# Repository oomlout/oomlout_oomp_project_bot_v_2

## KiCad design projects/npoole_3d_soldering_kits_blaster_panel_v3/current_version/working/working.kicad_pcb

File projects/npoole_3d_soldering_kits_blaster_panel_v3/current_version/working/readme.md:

# 3d_soldering_kits
 
## summary 
* id: npoole_3d_soldering_kits_blaster_panel_v3
* user: npoole
* name: 3d_soldering_kits
* board: blaster_panel_v3
* repo: https://github.com/NPoole/3D-Soldering-Kits

* src_file_repo_sch: 
* src_file_repo_sch_link: https://github.com/NPoole/3D-Soldering-Kits/tree/master/
* full details link: https://github.com/oomlout/oomlout_oomp_project_bot_v_2/tree/main/projects/npoole_3d_soldering_kits_blaster_panel_v3/current_version/working  

## pcb  

[board (pdf)](working.pdf)  

## working_bom
| Id | Designator | Footprint | Quantity | Designation | Supplier and ref |  | None | 
| --- | --- | --- | --- | --- | --- | --- | --- | 
| 1 | @HOLE20,@HOLE8,@HOLE134,@HOLE54,@HOLE166,@HOLE176,@HOLE216,@HOLE157,@HOLE70,@HOLE173,@HOLE236,@HOLE16,@HOLE103,@HOLE145,@HOLE208,@HOLE147,@HOLE37,@HOLE184,@HOLE240,@HOLE138,@HOLE17,@HOLE44,@HOLE24,@HOLE28,@HOLE160,@HOLE117,@HOLE25,@HOLE74,@HOLE239,@HOLE217,@HOLE214,@HOLE213,@HOLE237,@HOLE82,@HOLE142,@HOLE120,@HOLE137,@HOLE234,@HOLE39,@HOLE152,@HOLE66,@HOLE95,@HOLE194,@HOLE198,@HOLE182,@HOLE185,@HOLE193,@HOLE121,@HOLE87,@HOLE215,@HOLE183,@HOLE12,@HOLE69,@HOLE62,@HOLE132,@HOLE211,@HOLE169,@HOLE190,@HOLE94,@HOLE90,@HOLE104,@HOLE158,@HOLE33,@HOLE68,@HOLE0,@HOLE45,@HOLE57,@HOLE238,@HOLE170,@HOLE21,@HOLE187,@HOLE92,@HOLE77,@HOLE151,@HOLE123,@HOLE72,@HOLE52,@HOLE226,@HOLE202,@HOLE210,@HOLE65,@HOLE110,@HOLE206,@HOLE212,@HOLE18,@HOLE186,@HOLE47,@HOLE203,@HOLE165,@HOLE177,@HOLE75,@HOLE15,@HOLE23,@HOLE153,@HOLE84,@HOLE81,@HOLE108,@HOLE107,@HOLE150,@HOLE136,@HOLE11,@HOLE163,@HOLE10,@HOLE31,@HOLE48,@HOLE83,@HOLE96,@HOLE178,@HOLE9,@HOLE101,@HOLE102,@HOLE241,@HOLE51,@HOLE223,@HOLE172,@HOLE122,@HOLE219,@HOLE209,@HOLE7,@HOLE116,@HOLE56,@HOLE105,@HOLE118,@HOLE34,@HOLE38,@HOLE235,@HOLE230,@HOLE231,@HOLE164,@HOLE97,@HOLE40,@HOLE127,@HOLE124,@HOLE205,@HOLE168,@HOLE115,@HOLE2,@HOLE80,@HOLE29,@HOLE144,@HOLE159,@HOLE3,@HOLE106,@HOLE53,@HOLE61,@HOLE155,@HOLE200,@HOLE35,@HOLE4,@HOLE228,@HOLE148,@HOLE196,@HOLE207,@HOLE129,@HOLE146,@HOLE125,@HOLE218,@HOLE119,@HOLE175,@HOLE130,@HOLE59,@HOLE233,@HOLE63,@HOLE191,@HOLE13,@HOLE201,@HOLE86,@HOLE181,@HOLE100,@HOLE154,@HOLE131,@HOLE220,@HOLE67,@HOLE99,@HOLE41,@HOLE180,@HOLE188,@HOLE171,@HOLE46,@HOLE1,@HOLE76,@HOLE204,@HOLE174,@HOLE128,@HOLE71,@HOLE197,@HOLE98,@HOLE222,@HOLE79,@HOLE232,@HOLE30,@HOLE93,@HOLE14,@HOLE64,@HOLE162,@HOLE161,@HOLE139,@HOLE135,@HOLE224,@HOLE88,@HOLE89,@HOLE78,@HOLE91,@HOLE227,@HOLE32,@HOLE195,@HOLE26,@HOLE126,@HOLE27,@HOLE36,@HOLE60,@HOLE199,@HOLE192,@HOLE114,@HOLE133,@HOLE189,@HOLE42,@HOLE167,@HOLE225,@HOLE111,@HOLE141,@HOLE49,@HOLE179,@HOLE85,@HOLE112,@HOLE221,@HOLE149,@HOLE113,@HOLE55,@HOLE109,@HOLE19,@HOLE50,@HOLE73,@HOLE156,@HOLE6,@HOLE58,@HOLE143,@HOLE140,@HOLE43,@HOLE5,@HOLE229,@HOLE22 |  | 242 |  |  |  | [''] | 
| 2 | J2,J1 | 1X01 | 2 |  |  |  | [''] | 
| 3 | E$1 | GREATBIGFACTORYCLOUDLOGO#PNG | 1 |  |  |  | [''] | 
| 4 | U$1 | TEXT345#PNG | 1 |  |  |  | [''] | 
| 5 | R1,R2 | AXIAL-0.3 | 2 | 1k |  |  | [''] | 
| 6 | BT1 | BATTCON_20MM_4LEGS | 1 |  |  |  | [''] | 
| 7 | S1 | TACTILE_SWITCH_PTH_RIGHT_ANGLE_KIT | 1 | MOMENTARY-SWITCH-SPST-PTH-RIGHT-ANGLE-KIT |  |  | [''] |

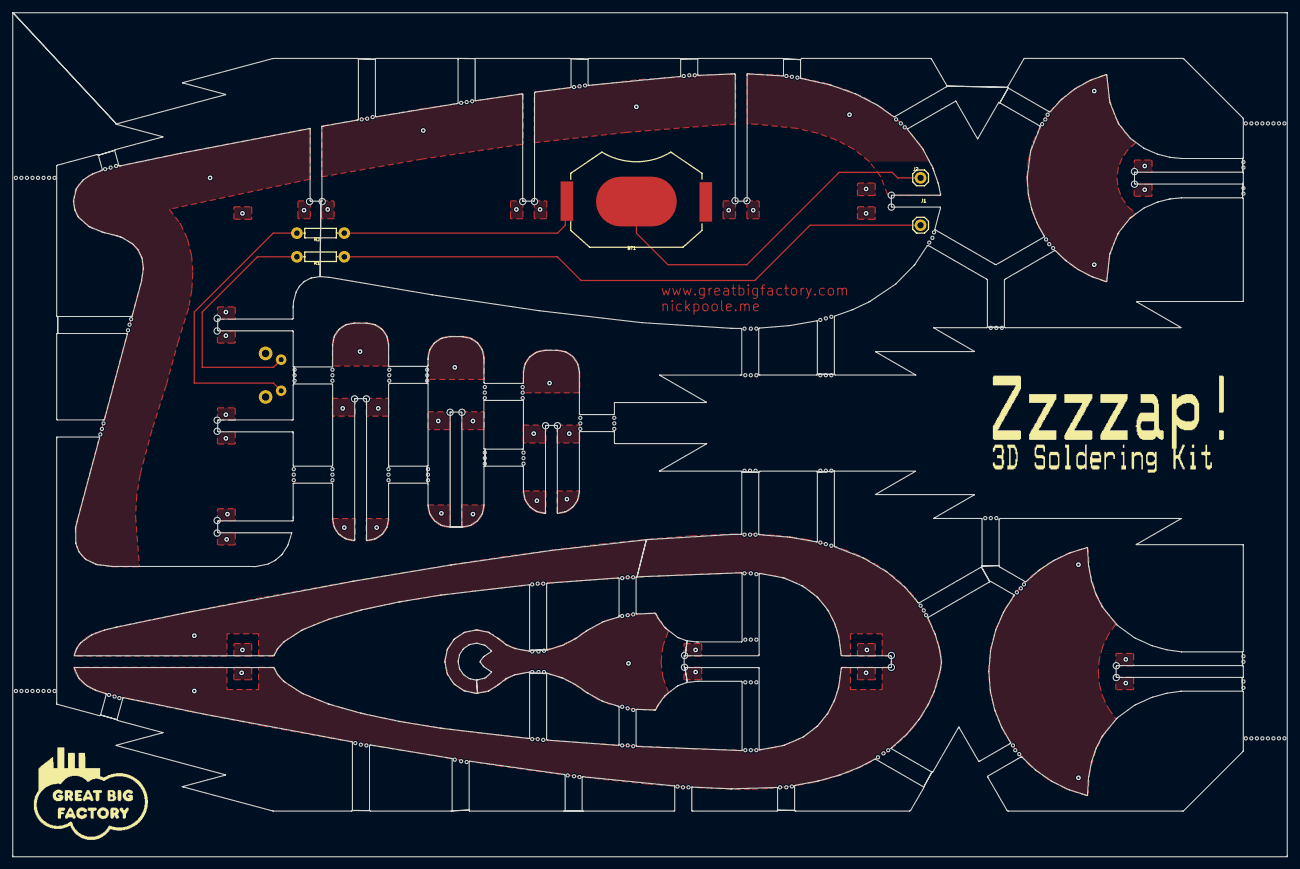
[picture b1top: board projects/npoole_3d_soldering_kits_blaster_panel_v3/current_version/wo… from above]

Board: 2 copper layers, 205.0 x 135.8 mm, 250 parts (1 on the bottom side), 5 nets.

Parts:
@HOLE0, @HOLE1, @HOLE2, @HOLE3, @HOLE4, @HOLE5, @HOLE6, @HOLE7, @HOLE8, @HOLE9, @HOLE10, @HOLE11, @HOLE12, @HOLE13, @HOLE14, @HOLE15, @HOLE16, @HOLE17, @HOLE18, @HOLE19, @HOLE20, @HOLE21, @HOLE22, @HOLE23, @HOLE24, @HOLE25, @HOLE26, @HOLE27, @HOLE28, @HOLE29, @HOLE30, @HOLE31, @HOLE32, @HOLE33, @HOLE34, @HOLE35, @HOLE36, @HOLE37, @HOLE38, @HOLE39, @HOLE40, @HOLE41, @HOLE42, @HOLE43, @HOLE44, @HOLE45, @HOLE46, @HOLE47, @HOLE48, @HOLE49, @HOLE50, @HOLE51, @HOLE52, @HOLE53, @HOLE54, @HOLE55, @HOLE56, @HOLE57, @HOLE58, @HOLE59, @HOLE60, @HOLE61, @HOLE62, @HOLE63, @HOLE64, @HOLE65, @HOLE66, @HOLE67, @HOLE68, @HOLE69, @HOLE70, @HOLE71, @HOLE72, @HOLE73, @HOLE74, @HOLE75, @HOLE76, @HOLE77, @HOLE78, @HOLE79, @HOLE80, @HOLE81, @HOLE82, @HOLE83, @HOLE84, @HOLE85, @HOLE86, @HOLE87, @HOLE88, @HOLE89, @HOLE90, @HOLE91, @HOLE92, @HOLE93, @HOLE94, @HOLE95, @HOLE96, @HOLE97, @HOLE98, @HOLE99, @HOLE100, @HOLE101, @HOLE102, @HOLE103, @HOLE104, @HOLE105, @HOLE106, @HOLE107, @HOLE108, @HOLE109, @HOLE110, @HOLE111, @HOLE112, @HOLE113, @HOLE114, @HOLE115, @HOLE116, @HOLE117, @HOLE118, @HOLE119, @HOLE120, @HOLE121, @HOLE122, @HOLE123, @HOLE124, @HOLE125, @HOLE126, @HOLE127, @HOLE128, @HOLE129, @HOLE130, @HOLE131, @HOLE132, @HOLE133, @HOLE134, @HOLE135, @HOLE136, @HOLE137, @HOLE138, @HOLE139, @HOLE140, @HOLE141, @HOLE142, @HOLE143, @HOLE144, @HOLE145, @HOLE146, @HOLE147, @HOLE148, @HOLE149, @HOLE150, @HOLE151, @HOLE152, @HOLE153, @HOLE154, @HOLE155, @HOLE156, @HOLE157, @HOLE158, @HOLE159, @HOLE160, @HOLE161, @HOLE162, @HOLE163, @HOLE164, @HOLE165, @HOLE166, @HOLE167, @HOLE168, @HOLE169, @HOLE170, @HOLE171, @HOLE172, @HOLE173, @HOLE174, @HOLE175, @HOLE176, @HOLE177, @HOLE178, @HOLE179, @HOLE180, @HOLE181, @HOLE182, @HOLE183, @HOLE184, @HOLE185, @HOLE186, @HOLE187, @HOLE188, @HOLE189, @HOLE190, @HOLE191, @HOLE192, @HOLE193, @HOLE194, @HOLE195, @HOLE196, @HOLE197, @HOLE198, @HOLE199, @HOLE200, @HOLE201, @HOLE202, @HOLE203, @HOLE204, @HOLE205, @HOLE206, @HOLE207, @HOLE208, @HOLE209, @HOLE210, @HOLE211, @HOLE212, @HOLE213, @HOLE214, @HOLE215, @HOLE216, @HOLE217, @HOLE218, @HOLE219, @HOLE220, @HOLE221, @HOLE222, @HOLE223, @HOLE224, @HOLE225, @HOLE226, @HOLE227, @HOLE228, @HOLE229, @HOLE230, @HOLE231, @HOLE232, @HOLE233, @HOLE234, @HOLE235, @HOLE236, @HOLE237, @HOLE238, @HOLE239, @HOLE240, @HOLE241: (no value)
BT1: BATTCON_20MM_4LEGS
E$1: GREATBIGFACTORYCLOUDLOGO#PNG
J1, J2: 1X01
R1, R2: 1k; AXIAL-0.3
S1: MOMENTARY-SWITCH-SPST-PTH-RIGHT-ANGLE-KIT; TACTILE_SWITCH_PTH_RIGHT_ANGLE_KIT
U$1: TEXT345#PNG

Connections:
GND: R1.P$2, S1.1
unnamed: BT1.POSITIVE@1, BT1.POSITIVE@2, BT1.POSITIVE@3, BT1.POSITIVE@4, R2.P$1
unnamed: J1.1, R1.P$1
unnamed: BT1.NEGATIVE, J2.1
unnamed: R2.P$2, S1.2

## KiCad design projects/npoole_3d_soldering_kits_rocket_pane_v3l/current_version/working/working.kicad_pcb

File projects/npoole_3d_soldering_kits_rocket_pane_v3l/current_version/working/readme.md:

# 3d_soldering_kits
 
## summary 
* id: npoole_3d_soldering_kits_rocket_pane_v3l
* user: npoole
* name: 3d_soldering_kits
* board: rocket_pane_v3l
* repo: https://github.com/NPoole/3D-Soldering-Kits

* src_file_repo_sch: 
* src_file_repo_sch_link: https://github.com/NPoole/3D-Soldering-Kits/tree/master/
* full details link: https://github.com/oomlout/oomlout_oomp_project_bot_v_2/tree/main/projects/npoole_3d_soldering_kits_rocket_pane_v3l/current_version/working  

## schematic  
  
[schematic (pdf)](working_schematic.pdf) 

## pcb  

[board (pdf)](working.pdf)  

## working_bom
| Id | Designator | Footprint | Quantity | Designation | Supplier and ref |  | None | 
| --- | --- | --- | --- | --- | --- | --- | --- | 
| 1 | @HOLE72,@HOLE63,@HOLE25,@HOLE85,@HOLE20,@HOLE17,@HOLE7,@HOLE42,@HOLE31,@HOLE70,@HOLE1,@HOLE32,@HOLE18,@HOLE49,@HOLE12,@HOLE64,@HOLE8,@HOLE89,@HOLE59,@HOLE4,@HOLE30,@HOLE29,@HOLE9,@HOLE80,@HOLE23,@HOLE83,@HOLE2,@HOLE33,@HOLE60,@HOLE41,@HOLE82,@HOLE56,@HOLE0,@HOLE90,@HOLE77,@HOLE19,@HOLE10,@HOLE43,@HOLE22,@HOLE15,@HOLE62,@HOLE58,@HOLE73,@HOLE57,@HOLE36,@HOLE27,@HOLE75,@HOLE66,@HOLE92,@HOLE45,@HOLE13,@HOLE94,@HOLE81,@HOLE68,@HOLE44,@HOLE3,@HOLE87,@HOLE24,@HOLE38,@HOLE61,@HOLE35,@HOLE88,@HOLE34,@HOLE76,@HOLE37,@HOLE11,@HOLE71,@HOLE5,@HOLE78,@HOLE53,@HOLE93,@HOLE28,@HOLE6,@HOLE54,@HOLE48,@HOLE51,@HOLE50,@HOLE79,@HOLE69,@HOLE84,@HOLE52,@HOLE91,@HOLE39,@HOLE47,@HOLE74,@HOLE21,@HOLE14,@HOLE65,@HOLE67,@HOLE16,@HOLE55,@HOLE40,@HOLE46,@HOLE86,@HOLE26 |  | 95 |  |  |  | [''] | 
| 2 | J1,J2 | 1X01 | 2 |  |  |  | [''] | 
| 3 | U$1 | TEXT1466#PNG | 1 |  |  |  | [''] | 
| 4 | U$2 | GREATBIGFACTORYCLOUDLOGO#PNG | 1 |  |  |  | [''] | 
| 5 | R1 | AXIAL-0.3 | 1 | 1k |  |  | [''] | 
| 6 | BT1 | BATTCON_20MM_4LEGS | 1 |  |  |  | [''] | 

## bom_schematic
| Ref | Qnty | Value | Cmp name | Footprint | Description | Vendor | DNP | 
| --- | --- | --- | --- | --- | --- | --- | --- | 
| BT1 | 1 | BATTERY-20MM_SMD_4LEGS | BATTERY-20MM_SMD_4LEGS | working:BATTCON_20MM_4LEGS |  |  |  | 
| J1, J2 | 2 | CONN_01 | CONN_01 | working:1X01 |  |  |  | 
| R1 | 1 | 1KOHM-HORIZ-1/4W-1% | 1KOHM-HORIZ-1/4W-1% | working:AXIAL-0.3 |  |  |  |

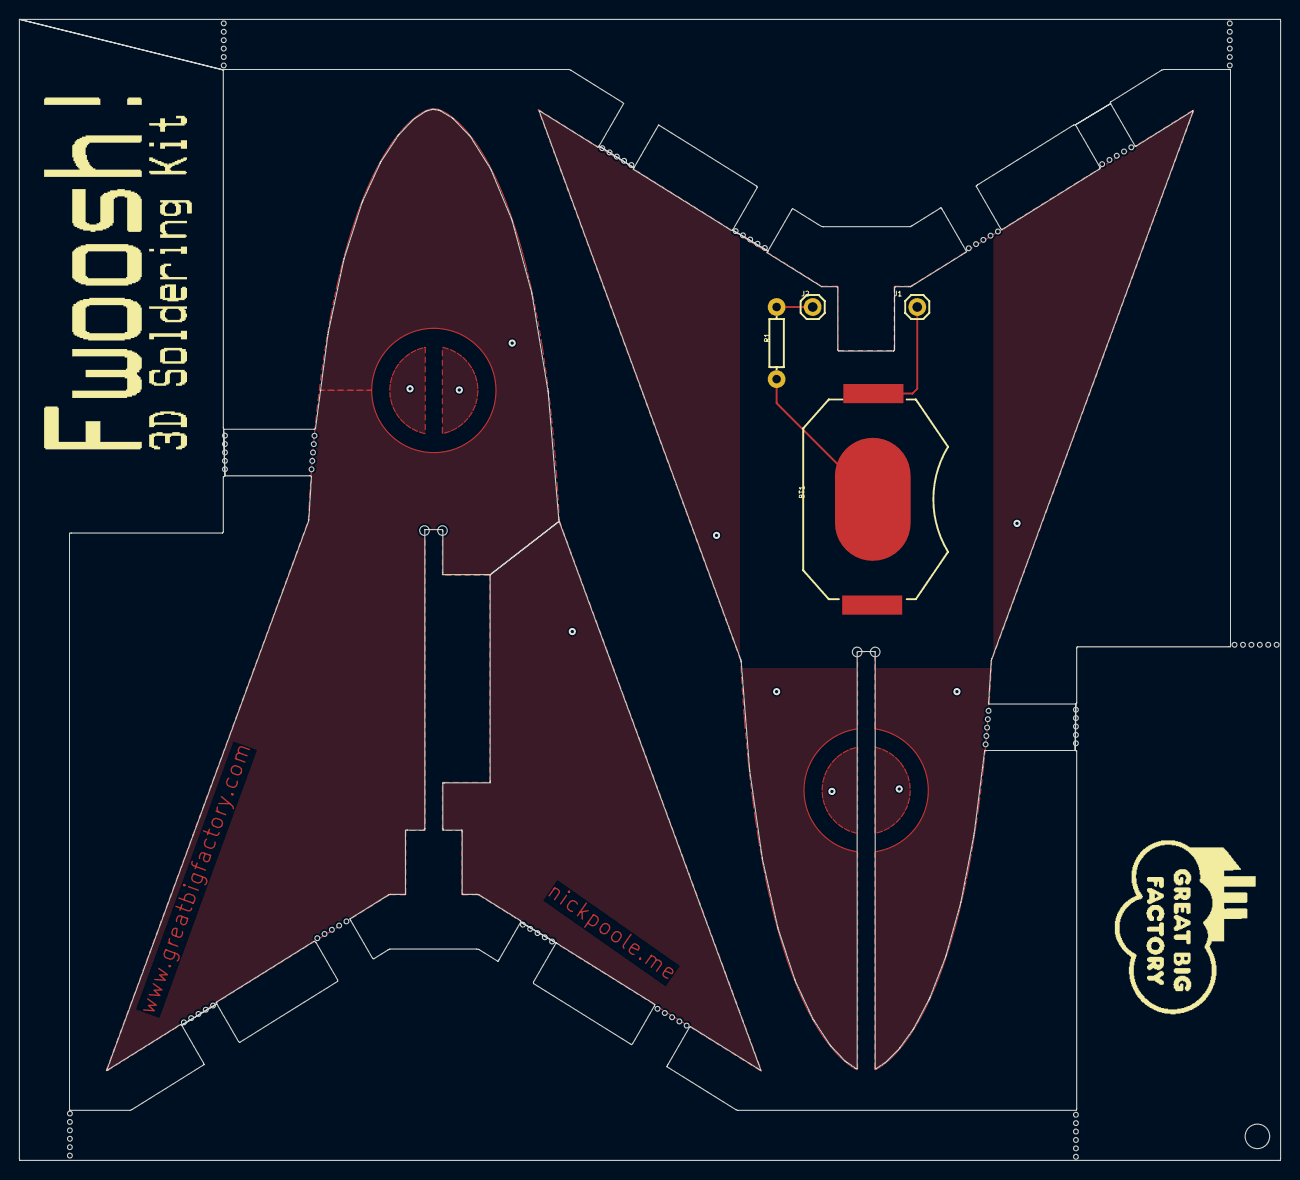
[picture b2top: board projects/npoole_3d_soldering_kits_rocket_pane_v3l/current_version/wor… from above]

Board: 2 copper layers, 133.3 x 120.6 mm, 101 parts (0 on the bottom side), 3 nets.

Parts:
@HOLE0, @HOLE1, @HOLE2, @HOLE3, @HOLE4, @HOLE5, @HOLE6, @HOLE7, @HOLE8, @HOLE9, @HOLE10, @HOLE11, @HOLE12, @HOLE13, @HOLE14, @HOLE15, @HOLE16, @HOLE17, @HOLE18, @HOLE19, @HOLE20, @HOLE21, @HOLE22, @HOLE23, @HOLE24, @HOLE25, @HOLE26, @HOLE27, @HOLE28, @HOLE29, @HOLE30, @HOLE31, @HOLE32, @HOLE33, @HOLE34, @HOLE35, @HOLE36, @HOLE37, @HOLE38, @HOLE39, @HOLE40, @HOLE41, @HOLE42, @HOLE43, @HOLE44, @HOLE45, @HOLE46, @HOLE47, @HOLE48, @HOLE49, @HOLE50, @HOLE51, @HOLE52, @HOLE53, @HOLE54, @HOLE55, @HOLE56, @HOLE57, @HOLE58, @HOLE59, @HOLE60, @HOLE61, @HOLE62, @HOLE63, @HOLE64, @HOLE65, @HOLE66, @HOLE67, @HOLE68, @HOLE69, @HOLE70, @HOLE71, @HOLE72, @HOLE73, @HOLE74, @HOLE75, @HOLE76, @HOLE77, @HOLE78, @HOLE79, @HOLE80, @HOLE81, @HOLE82, @HOLE83, @HOLE84, @HOLE85, @HOLE86, @HOLE87, @HOLE88, @HOLE89, @HOLE90, @HOLE91, @HOLE92, @HOLE93, @HOLE94: (no value)
BT1: BATTCON_20MM_4LEGS
J1, J2: 1X01
R1: 1k; AXIAL-0.3
U$1: TEXT1466#PNG
U$2: GREATBIGFACTORYCLOUDLOGO#PNG

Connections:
GND: J2.1, R1.P$2
GND1: BT1.NEGATIVE, R1.P$1
unnamed: BT1.POSITIVE@1, BT1.POSITIVE@2, BT1.POSITIVE@3, BT1.POSITIVE@4, J1.1

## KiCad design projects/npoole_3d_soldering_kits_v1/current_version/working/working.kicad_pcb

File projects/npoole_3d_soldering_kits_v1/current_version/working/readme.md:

# 3d_soldering_kits
 
## summary 
* id: npoole_3d_soldering_kits_v1
* user: npoole
* name: 3d_soldering_kits
* board: v1
* repo: https://github.com/NPoole/3D-Soldering-Kits

* src_file_repo_sch: 
* src_file_repo_sch_link: https://github.com/NPoole/3D-Soldering-Kits/tree/master/
* full details link: https://github.com/oomlout/oomlout_oomp_project_bot_v_2/tree/main/projects/npoole_3d_soldering_kits_v1/current_version/working  

## schematic  
  
[schematic (pdf)](working_schematic.pdf) 

## pcb  

[board (pdf)](working.pdf)  

## working_bom
| Id | Designator | Footprint | Quantity | Designation | Supplier and ref |  | None | 
| --- | --- | --- | --- | --- | --- | --- | --- | 
| 1 | @HOLE23,@HOLE17,@HOLE12,@HOLE29,@HOLE19,@HOLE13,@HOLE5,@HOLE38,@HOLE14,@HOLE3,@HOLE24,@HOLE22,@HOLE34,@HOLE37,@HOLE21,@HOLE36,@HOLE39,@HOLE4,@HOLE11,@HOLE33,@HOLE25,@HOLE28,@HOLE27,@HOLE10,@HOLE15,@HOLE1,@HOLE30,@HOLE2,@HOLE35,@HOLE0,@HOLE32,@HOLE31,@HOLE8,@HOLE7,@HOLE9,@HOLE18,@HOLE40,@HOLE6,@HOLE16,@HOLE20,@HOLE26 |  | 41 |  |  |  | [''] | 
| 2 | BT1 | BATTCON_20MM_4LEGS | 1 |  |  |  | [''] | 
| 3 | R1 | AXIAL-0.3 | 1 | 1k |  |  | [''] | 
| 4 | D1 | LED_5MM | 1 |  |  |  | [''] | 
| 5 | S1 | TACTILE_SWITCH_PTH_6.0MM | 1 | MOMENTARY-SWITCH-SPST-PTH-6.0MM |  |  | [''] | 

## bom_schematic
| Ref | Qnty | Value | Cmp name | Footprint | Description | Vendor | DNP | 
| --- | --- | --- | --- | --- | --- | --- | --- | 
| BT1 | 1 | BATTERY-20MM_SMD_4LEGS | BATTERY-20MM_SMD_4LEGS | working:BATTCON_20MM_4LEGS |  |  |  | 
| D1 | 1 | LED5MM | LED5MM | working:LED_5MM |  |  |  | 
| R1 | 1 | 1KOHM-HORIZ-1/4W-1% | 1KOHM-HORIZ-1/4W-1% | working:AXIAL-0.3 |  |  |  | 
| S1 | 1 | MOMENTARY-SWITCH-SPST-PTH-6.0MM | MOMENTARY-SWITCH-SPST-PTH-6.0MM | working:TACTILE_SWITCH_PTH_6.0MM |  |  |  |

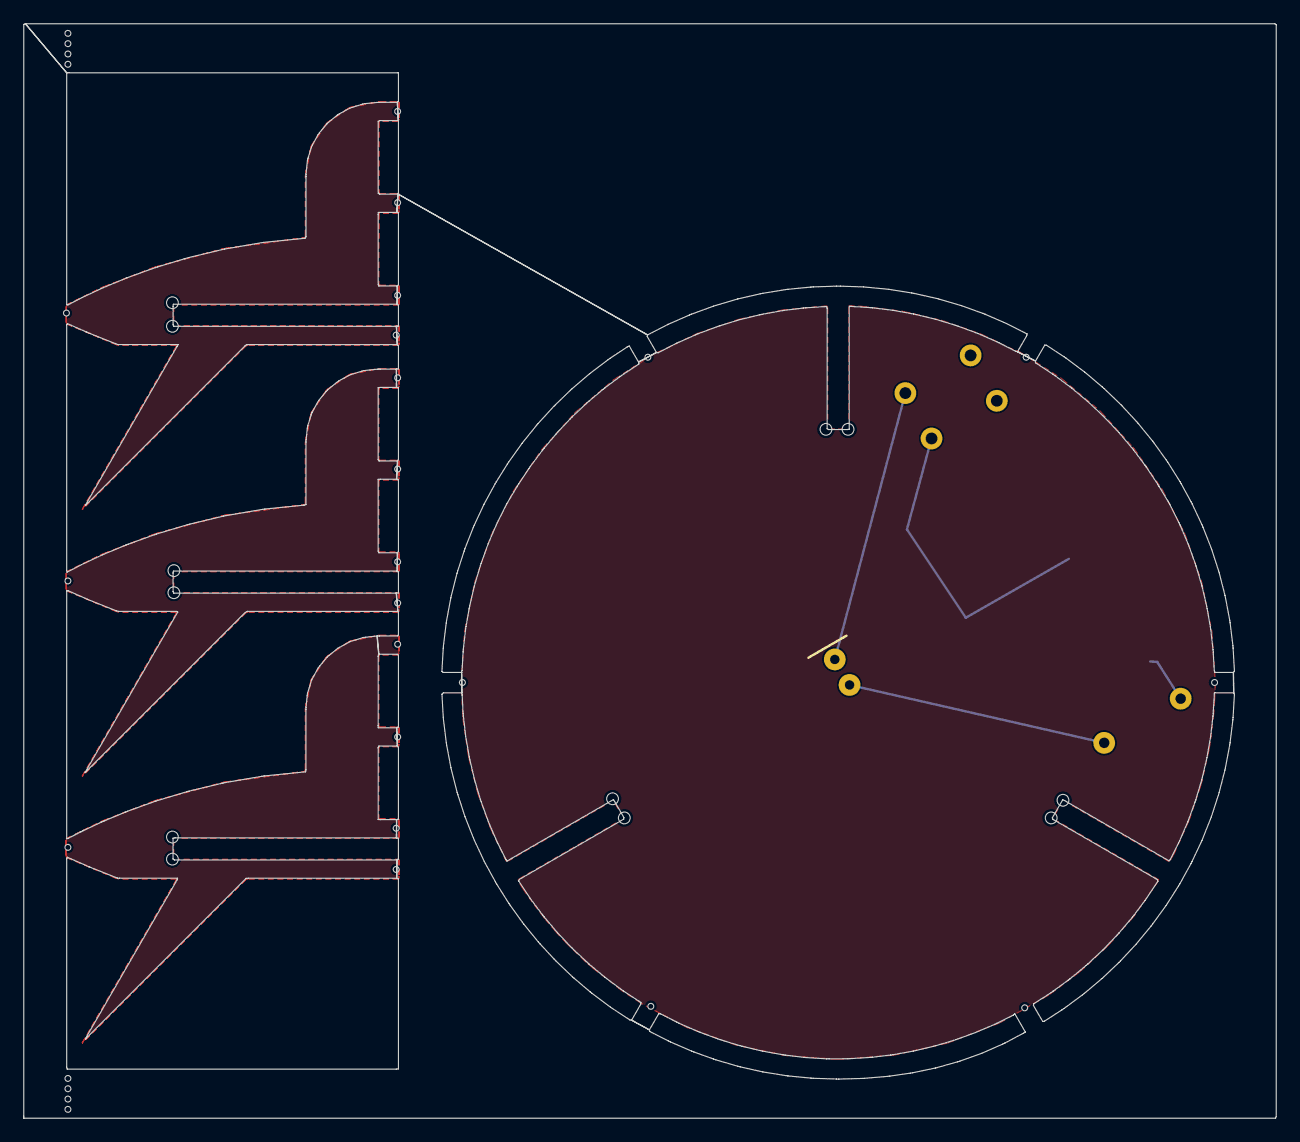
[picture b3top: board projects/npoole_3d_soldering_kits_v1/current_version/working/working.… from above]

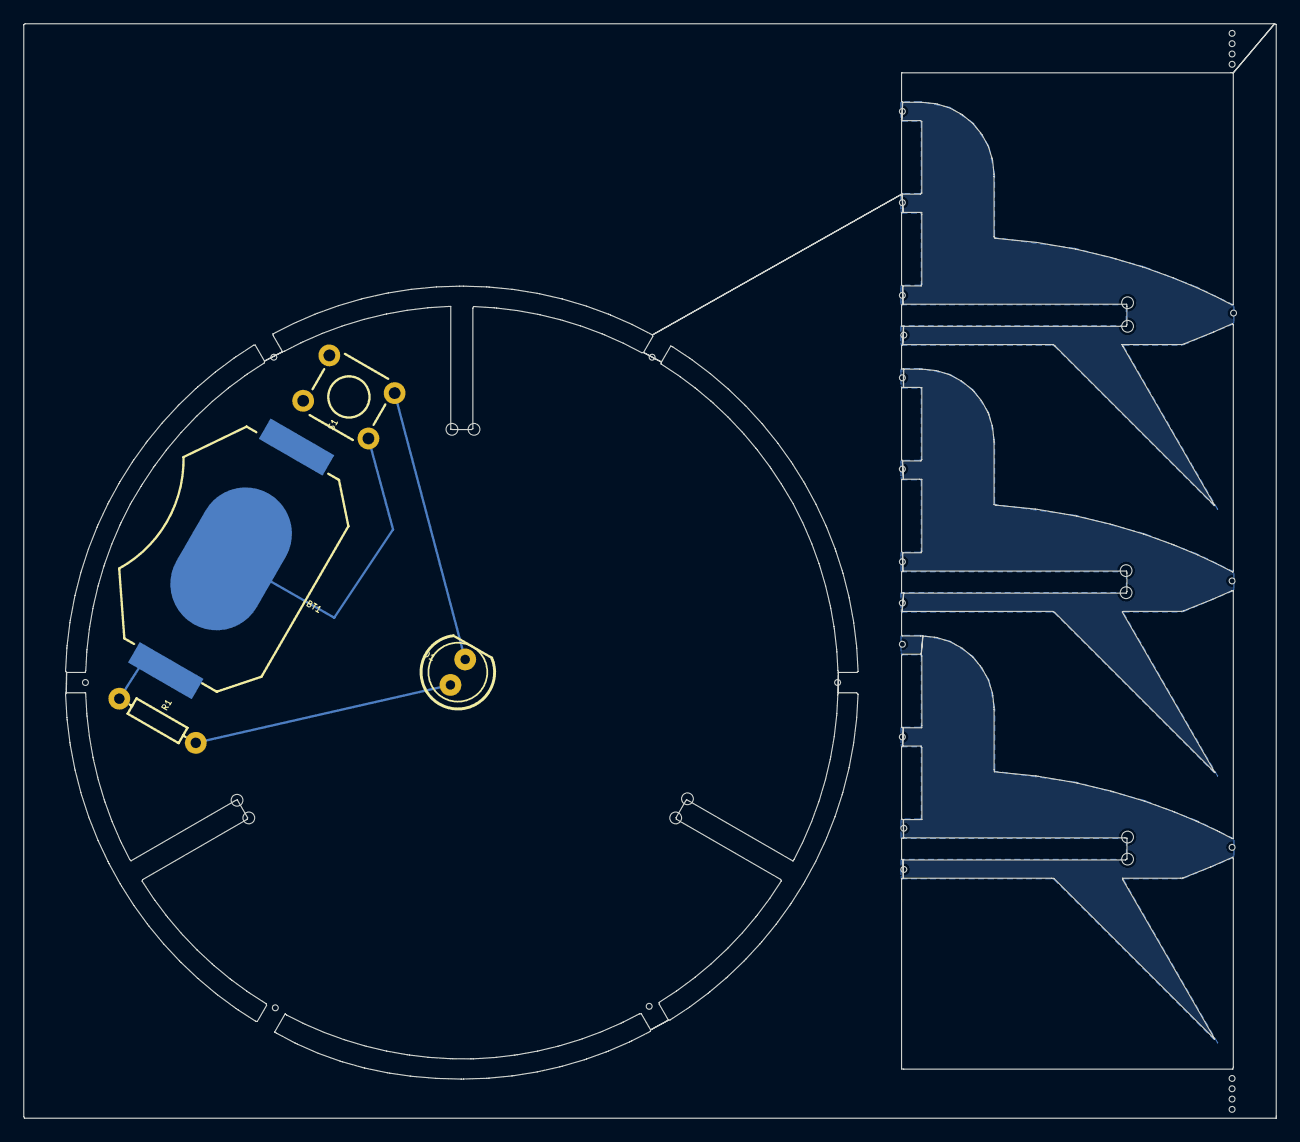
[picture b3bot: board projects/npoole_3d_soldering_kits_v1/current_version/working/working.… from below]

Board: 2 copper layers, 108.1 x 94.4 mm, 45 parts (4 on the bottom side), 4 nets.

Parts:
@HOLE0, @HOLE1, @HOLE2, @HOLE3, @HOLE4, @HOLE5, @HOLE6, @HOLE7, @HOLE8, @HOLE9, @HOLE10, @HOLE11, @HOLE12, @HOLE13, @HOLE14, @HOLE15, @HOLE16, @HOLE17, @HOLE18, @HOLE19, @HOLE20, @HOLE21, @HOLE22, @HOLE23, @HOLE24, @HOLE25, @HOLE26, @HOLE27, @HOLE28, @HOLE29, @HOLE30, @HOLE31, @HOLE32, @HOLE33, @HOLE34, @HOLE35, @HOLE36, @HOLE37, @HOLE38, @HOLE39, @HOLE40: (no value)
BT1: BATTCON_20MM_4LEGS
D1: LED_5MM
R1: 1k; AXIAL-0.3
S1: MOMENTARY-SWITCH-SPST-PTH-6.0MM; TACTILE_SWITCH_PTH_6.0MM

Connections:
GND: BT1.POSITIVE@1, BT1.POSITIVE@2, BT1.POSITIVE@3, BT1.POSITIVE@4, R1.P$1
unnamed: D1.A, R1.P$2
unnamed: BT1.NEGATIVE, S1.1
unnamed: D1.K, S1.3

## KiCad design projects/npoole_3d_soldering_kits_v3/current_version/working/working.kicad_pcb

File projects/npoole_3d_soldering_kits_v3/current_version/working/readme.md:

# 3d_soldering_kits
 
## summary 
* id: npoole_3d_soldering_kits_v3
* user: npoole
* name: 3d_soldering_kits
* board: v3
* repo: https://github.com/NPoole/3D-Soldering-Kits

* src_file_repo_sch: 
* src_file_repo_sch_link: https://github.com/NPoole/3D-Soldering-Kits/tree/master/
* full details link: https://github.com/oomlout/oomlout_oomp_project_bot_v_2/tree/main/projects/npoole_3d_soldering_kits_v3/current_version/working  

## schematic  
  
[schematic (pdf)](working_schematic.pdf) 

## pcb  

[board (pdf)](working.pdf)  

## working_bom
| Id | Designator | Footprint | Quantity | Designation | Supplier and ref |  | None | 
| --- | --- | --- | --- | --- | --- | --- | --- | 
| 1 | @HOLE198,@HOLE122,@HOLE124,@HOLE74,@HOLE68,@HOLE293,@HOLE29,@HOLE268,@HOLE221,@HOLE226,@HOLE330,@HOLE295,@HOLE11,@HOLE0,@HOLE292,@HOLE49,@HOLE169,@HOLE306,@HOLE328,@HOLE65,@HOLE195,@HOLE93,@HOLE17,@HOLE213,@HOLE69,@HOLE199,@HOLE212,@HOLE339,@HOLE319,@HOLE321,@HOLE345,@HOLE323,@HOLE96,@HOLE190,@HOLE119,@HOLE149,@HOLE239,@HOLE55,@HOLE252,@HOLE281,@HOLE249,@HOLE51,@HOLE137,@HOLE34,@HOLE223,@HOLE6,@HOLE318,@HOLE114,@HOLE154,@HOLE176,@HOLE66,@HOLE23,@HOLE151,@HOLE141,@HOLE348,@HOLE121,@HOLE326,@HOLE184,@HOLE274,@HOLE225,@HOLE344,@HOLE165,@HOLE88,@HOLE83,@HOLE217,@HOLE276,@HOLE110,@HOLE234,@HOLE331,@HOLE204,@HOLE336,@HOLE316,@HOLE286,@HOLE75,@HOLE16,@HOLE76,@HOLE206,@HOLE220,@HOLE258,@HOLE333,@HOLE216,@HOLE174,@HOLE25,@HOLE7,@HOLE296,@HOLE56,@HOLE39,@HOLE235,@HOLE73,@HOLE192,@HOLE191,@HOLE325,@HOLE92,@HOLE297,@HOLE134,@HOLE289,@HOLE143,@HOLE243,@HOLE130,@HOLE131,@HOLE311,@HOLE236,@HOLE257,@HOLE32,@HOLE324,@HOLE327,@HOLE218,@HOLE335,@HOLE260,@HOLE85,@HOLE123,@HOLE244,@HOLE248,@HOLE167,@HOLE26,@HOLE282,@HOLE41,@HOLE105,@HOLE44,@HOLE322,@HOLE70,@HOLE147,@HOLE175,@HOLE80,@HOLE156,@HOLE181,@HOLE253,@HOLE47,@HOLE72,@HOLE201,@HOLE37,@HOLE126,@HOLE273,@HOLE15,@HOLE270,@HOLE298,@HOLE310,@HOLE1,@HOLE22,@HOLE303,@HOLE254,@HOLE67,@HOLE351,@HOLE132,@HOLE307,@HOLE205,@HOLE152,@HOLE118,@HOLE317,@HOLE62,@HOLE84,@HOLE271,@HOLE78,@HOLE247,@HOLE64,@HOLE229,@HOLE101,@HOLE30,@HOLE280,@HOLE340,@HOLE211,@HOLE179,@HOLE71,@HOLE54,@HOLE3,@HOLE230,@HOLE48,@HOLE86,@HOLE278,@HOLE99,@HOLE103,@HOLE180,@HOLE28,@HOLE309,@HOLE133,@HOLE148,@HOLE238,@HOLE104,@HOLE46,@HOLE241,@HOLE50,@HOLE97,@HOLE102,@HOLE188,@HOLE337,@HOLE117,@HOLE285,@HOLE136,@HOLE266,@HOLE43,@HOLE269,@HOLE5,@HOLE246,@HOLE82,@HOLE349,@HOLE170,@HOLE187,@HOLE145,@HOLE129,@HOLE203,@HOLE263,@HOLE178,@HOLE305,@HOLE304,@HOLE127,@HOLE262,@HOLE272,@HOLE341,@HOLE125,@HOLE202,@HOLE163,@HOLE287,@HOLE251,@HOLE87,@HOLE312,@HOLE231,@HOLE94,@HOLE291,@HOLE222,@HOLE294,@HOLE31,@HOLE95,@HOLE33,@HOLE320,@HOLE106,@HOLE259,@HOLE255,@HOLE347,@HOLE208,@HOLE290,@HOLE210,@HOLE140,@HOLE334,@HOLE207,@HOLE302,@HOLE279,@HOLE250,@HOLE45,@HOLE177,@HOLE314,@HOLE267,@HOLE40,@HOLE299,@HOLE135,@HOLE57,@HOLE91,@HOLE242,@HOLE18,@HOLE313,@HOLE162,@HOLE52,@HOLE35,@HOLE265,@HOLE329,@HOLE301,@HOLE21,@HOLE308,@HOLE160,@HOLE100,@HOLE115,@HOLE107,@HOLE338,@HOLE300,@HOLE108,@HOLE90,@HOLE166,@HOLE197,@HOLE142,@HOLE79,@HOLE228,@HOLE81,@HOLE10,@HOLE193,@HOLE346,@HOLE168,@HOLE315,@HOLE27,@HOLE158,@HOLE240,@HOLE350,@HOLE264,@HOLE98,@HOLE36,@HOLE342,@HOLE144,@HOLE111,@HOLE128,@HOLE164,@HOLE12,@HOLE61,@HOLE185,@HOLE58,@HOLE209,@HOLE138,@HOLE146,@HOLE237,@HOLE2,@HOLE277,@HOLE60,@HOLE113,@HOLE13,@HOLE8,@HOLE63,@HOLE183,@HOLE283,@HOLE4,@HOLE196,@HOLE9,@HOLE214,@HOLE219,@HOLE89,@HOLE172,@HOLE150,@HOLE288,@HOLE224,@HOLE186,@HOLE53,@HOLE59,@HOLE256,@HOLE284,@HOLE157,@HOLE332,@HOLE24,@HOLE227,@HOLE20,@HOLE112,@HOLE171,@HOLE116,@HOLE14,@HOLE38,@HOLE194,@HOLE161,@HOLE109,@HOLE159,@HOLE120,@HOLE233,@HOLE215,@HOLE200,@HOLE343,@HOLE42,@HOLE261,@HOLE275,@HOLE189,@HOLE77,@HOLE153,@HOLE139,@HOLE182,@HOLE155,@HOLE173,@HOLE19,@HOLE232,@HOLE245 |  | 352 |  |  |  | [''] | 
| 2 | U$2 | RECT1468#PNG | 1 |  |  |  | [''] | 
| 3 | U$1 | GREATBIGFACTORYCLOUDLOGO#PNG | 1 | GREATBIGFACTORYCLOUDLOGO#PNG |  |  | [''] | 
| 4 | D3,D4 | LED_5MM | 2 |  |  |  | [''] | 
| 5 | S2 | SWITCH_SPDT_PTH_11.6X4.0MM_KIT | 1 |  |  |  | [''] | 
| 6 | R4,R3 | AXIAL-0.3EZ | 2 | 100 |  |  | [''] | 
| 7 | BT2 | BATTCOM_20MM_PTH_KIT | 1 |  |  |  | [''] | 

## bom_schematic
| Ref | Qnty | Value | Cmp name | Footprint | Description | Vendor | DNP | 
| --- | --- | --- | --- | --- | --- | --- | --- | 
| BT2 | 1 | BATTERY-20MM_PTH_KIT | BATTERY-20MM_PTH_KIT | working:BATTCOM_20MM_PTH_KIT |  |  |  | 
| D3, D4 | 2 | LED5MM | LED5MM | working:LED_5MM |  |  |  | 
| R3, R4 | 2 | 100OHM-HORIZ_KIT-1/4W-1% | 100OHM-HORIZ_KIT-1/4W-1% | working:AXIAL-0.3EZ |  |  |  | 
| S2 | 1 | SWITCH-SPDT-PTH-11.6X4.0MM-KIT | SWITCH-SPDT-PTH-11.6X4.0MM-KIT | working:SWITCH_SPDT_PTH_11.6X4.0MM_KIT |  |  |  | 
| U$1 | 1 | GREATBIGFACTORYCLOUDLOGO#PNG | GREATBIGFACTORYCLOUDLOGO#PNG | working:GREATBIGFACTORYCLOUDLOGO#PNG |  |  |  |

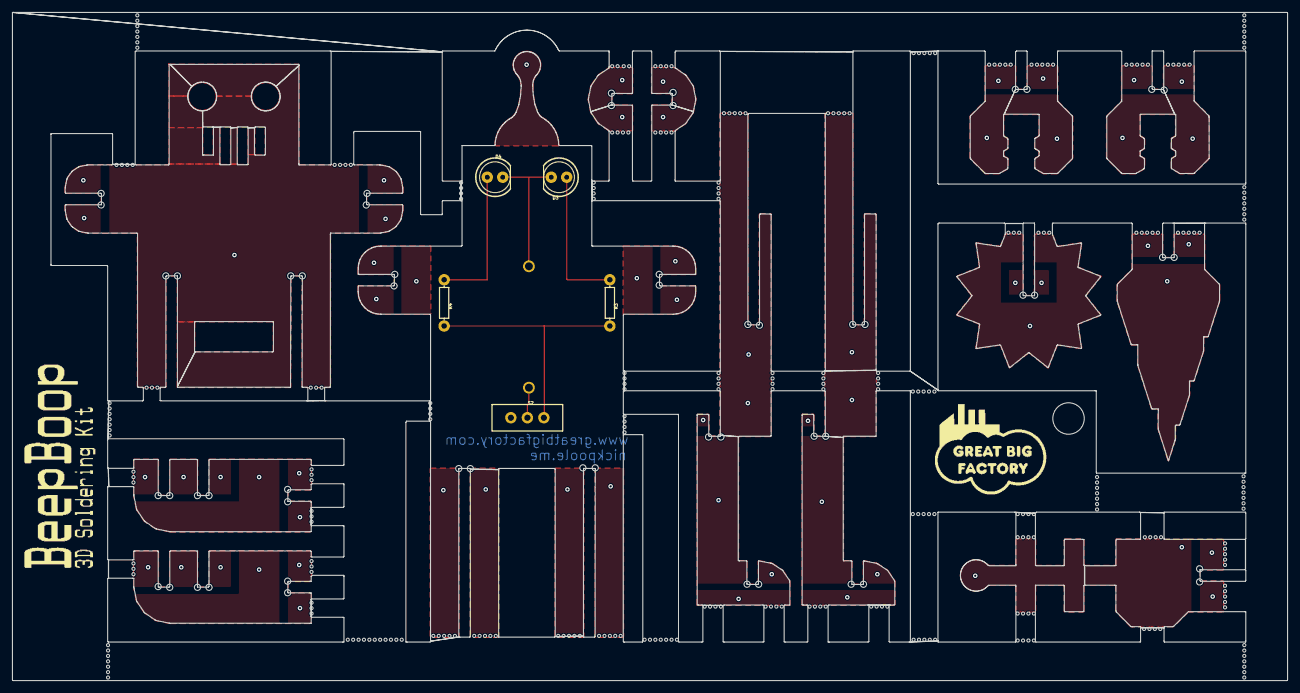
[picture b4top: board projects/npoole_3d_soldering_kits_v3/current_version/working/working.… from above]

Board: 2 copper layers, 210.1 x 110.1 mm, 360 parts (1 on the bottom side), 5 nets.

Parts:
@HOLE0, @HOLE1, @HOLE2, @HOLE3, @HOLE4, @HOLE5, @HOLE6, @HOLE7, @HOLE8, @HOLE9, @HOLE10, @HOLE11, @HOLE12, @HOLE13, @HOLE14, @HOLE15, @HOLE16, @HOLE17, @HOLE18, @HOLE19, @HOLE20, @HOLE21, @HOLE22, @HOLE23, @HOLE24, @HOLE25, @HOLE26, @HOLE27, @HOLE28, @HOLE29, @HOLE30, @HOLE31, @HOLE32, @HOLE33, @HOLE34, @HOLE35, @HOLE36, @HOLE37, @HOLE38, @HOLE39, @HOLE40, @HOLE41, @HOLE42, @HOLE43, @HOLE44, @HOLE45, @HOLE46, @HOLE47, @HOLE48, @HOLE49, @HOLE50, @HOLE51, @HOLE52, @HOLE53, @HOLE54, @HOLE55, @HOLE56, @HOLE57, @HOLE58, @HOLE59, @HOLE60, @HOLE61, @HOLE62, @HOLE63, @HOLE64, @HOLE65, @HOLE66, @HOLE67, @HOLE68, @HOLE69, @HOLE70, @HOLE71, @HOLE72, @HOLE73, @HOLE74, @HOLE75, @HOLE76, @HOLE77, @HOLE78, @HOLE79, @HOLE80, @HOLE81, @HOLE82, @HOLE83, @HOLE84, @HOLE85, @HOLE86, @HOLE87, @HOLE88, @HOLE89, @HOLE90, @HOLE91, @HOLE92, @HOLE93, @HOLE94, @HOLE95, @HOLE96, @HOLE97, @HOLE98, @HOLE99, @HOLE100, @HOLE101, @HOLE102, @HOLE103, @HOLE104, @HOLE105, @HOLE106, @HOLE107, @HOLE108, @HOLE109, @HOLE110, @HOLE111, @HOLE112, @HOLE113, @HOLE114, @HOLE115, @HOLE116, @HOLE117, @HOLE118, @HOLE119, @HOLE120, @HOLE121, @HOLE122, @HOLE123, @HOLE124, @HOLE125, @HOLE126, @HOLE127, @HOLE128, @HOLE129, @HOLE130, @HOLE131, @HOLE132, @HOLE133, @HOLE134, @HOLE135, @HOLE136, @HOLE137, @HOLE138, @HOLE139, @HOLE140, @HOLE141, @HOLE142, @HOLE143, @HOLE144, @HOLE145, @HOLE146, @HOLE147, @HOLE148, @HOLE149, @HOLE150, @HOLE151, @HOLE152, @HOLE153, @HOLE154, @HOLE155, @HOLE156, @HOLE157, @HOLE158, @HOLE159, @HOLE160, @HOLE161, @HOLE162, @HOLE163, @HOLE164, @HOLE165, @HOLE166, @HOLE167, @HOLE168, @HOLE169, @HOLE170, @HOLE171, @HOLE172, @HOLE173, @HOLE174, @HOLE175, @HOLE176, @HOLE177, @HOLE178, @HOLE179, @HOLE180, @HOLE181, @HOLE182, @HOLE183, @HOLE184, @HOLE185, @HOLE186, @HOLE187, @HOLE188, @HOLE189, @HOLE190, @HOLE191, @HOLE192, @HOLE193, @HOLE194, @HOLE195, @HOLE196, @HOLE197, @HOLE198, @HOLE199, @HOLE200, @HOLE201, @HOLE202, @HOLE203, @HOLE204, @HOLE205, @HOLE206, @HOLE207, @HOLE208, @HOLE209, @HOLE210, @HOLE211, @HOLE212, @HOLE213, @HOLE214, @HOLE215, @HOLE216, @HOLE217, @HOLE218, @HOLE219, @HOLE220, @HOLE221, @HOLE222, @HOLE223, @HOLE224, @HOLE225, @HOLE226, @HOLE227, @HOLE228, @HOLE229, @HOLE230, @HOLE231, @HOLE232, @HOLE233, @HOLE234, @HOLE235, @HOLE236, @HOLE237, @HOLE238, @HOLE239, @HOLE240, @HOLE241, @HOLE242, @HOLE243, @HOLE244, @HOLE245, @HOLE246, @HOLE247, @HOLE248, @HOLE249, @HOLE250, @HOLE251, @HOLE252, @HOLE253, @HOLE254, @HOLE255, @HOLE256, @HOLE257, @HOLE258, @HOLE259, @HOLE260, @HOLE261, @HOLE262, @HOLE263, @HOLE264, @HOLE265, @HOLE266, @HOLE267, @HOLE268, @HOLE269, @HOLE270, @HOLE271, @HOLE272, @HOLE273, @HOLE274, @HOLE275, @HOLE276, @HOLE277, @HOLE278, @HOLE279, @HOLE280, @HOLE281, @HOLE282, @HOLE283, @HOLE284, @HOLE285, @HOLE286, @HOLE287, @HOLE288, @HOLE289, @HOLE290, @HOLE291, @HOLE292, @HOLE293, @HOLE294, @HOLE295, @HOLE296, @HOLE297, @HOLE298, @HOLE299, @HOLE300, @HOLE301, @HOLE302, @HOLE303, @HOLE304, @HOLE305, @HOLE306, @HOLE307, @HOLE308, @HOLE309, @HOLE310, @HOLE311, @HOLE312, @HOLE313, @HOLE314, @HOLE315, @HOLE316, @HOLE317, @HOLE318, @HOLE319, @HOLE320, @HOLE321, @HOLE322, @HOLE323, @HOLE324, @HOLE325, @HOLE326, @HOLE327, @HOLE328, @HOLE329, @HOLE330, @HOLE331, @HOLE332, @HOLE333, @HOLE334, @HOLE335, @HOLE336, @HOLE337, @HOLE338, @HOLE339, @HOLE340, @HOLE341, @HOLE342, @HOLE343, @HOLE344, @HOLE345, @HOLE346, @HOLE347, @HOLE348, @HOLE349, @HOLE350, @HOLE351: (no value)
BT2: BATTCOM_20MM_PTH_KIT
D3, D4: LED_5MM
R3, R4: 100; AXIAL-0.3EZ
S2: SWITCH_SPDT_PTH_11.6X4.0MM_KIT
U$1: GREATBIGFACTORYCLOUDLOGO#PNG
U$2: RECT1468#PNG

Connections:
S$1: BT2.1, S2.2
S$2: BT2.2, D3.K, D4.K
S$3: R3.P$2, R4.P$2, S2.1
S$4: D4.A, R4.P$1
S$5: D3.A, R3.P$1

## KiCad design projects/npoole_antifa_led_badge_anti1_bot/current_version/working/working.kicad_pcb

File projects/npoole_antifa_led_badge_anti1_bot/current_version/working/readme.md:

# antifa_led_badge
 
## summary 
* id: npoole_antifa_led_badge_anti1_bot
* user: npoole
* name: antifa_led_badge
* board: anti1_bot
* repo: https://github.com/NPoole/Antifa_LED_Badge

* src_file_repo_sch: 
* src_file_repo_sch_link: https://github.com/NPoole/Antifa_LED_Badge/tree/master/
* full details link: https://github.com/oomlout/oomlout_oomp_project_bot_v_2/tree/main/projects/npoole_antifa_led_badge_anti1_bot/current_version/working  

## schematic  
  
[schematic (pdf)](working_schematic.pdf) 

## pcb  

[board (pdf)](working.pdf)  

## working_bom
| Id | Designator | Footprint | Quantity | Designation | Supplier and ref |  | None | 
| --- | --- | --- | --- | --- | --- | --- | --- | 
| 1 | D8,D7,D4,D3,D2,D1,D5,D6 | LED-0603 | 8 |  |  |  | [''] | 
| 2 | R5,R4,R6,R2,R8,R3,R7,R1 | 0603 | 8 | 33 |  |  | [''] | 
| 3 | E$3,E$4 | 1X01_NO_SILK | 2 |  |  |  | [''] | 
| 4 | S1 | SWITCH_DPDT_SMD_AYZ0202 | 1 |  |  |  | [''] | 
| 5 | BT1 | BATTCON_20MM_4LEGS | 1 |  |  |  | [''] | 

## bom_schematic
| Ref | Qnty | Value | Cmp name | Footprint | Description | Vendor | DNP | 
| --- | --- | --- | --- | --- | --- | --- | --- | 
| BT1 | 1 | BATTERY-20MM_SMD_4LEGS | BATTERY-20MM_SMD_4LEGS | working:BATTCON_20MM_4LEGS |  |  |  | 
| D1, D2, D3, D4, D5, D6, D7, D8 | 8 | LED0603 | LED0603 | working:LED-0603 |  |  |  | 
| R1, R2, R3, R4, R5, R6, R7, R8 | 8 | 33OHM-0603-1/10W-1% | 33OHM-0603-1/10W-1% | working:0603 |  |  |  | 
| S1 | 1 | SWITCH-SPDT-SMD-AYZ0202 | SWITCH-SPDT-SMD-AYZ0202 | working:SWITCH_DPDT_SMD_AYZ0202 |  |  |  |

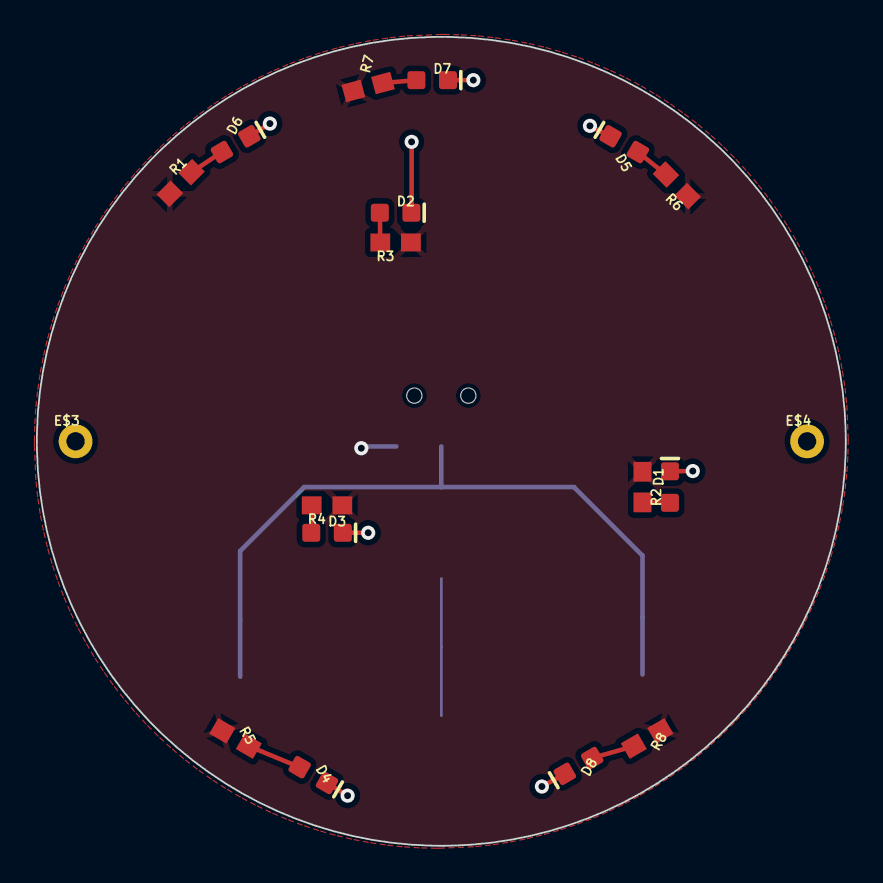
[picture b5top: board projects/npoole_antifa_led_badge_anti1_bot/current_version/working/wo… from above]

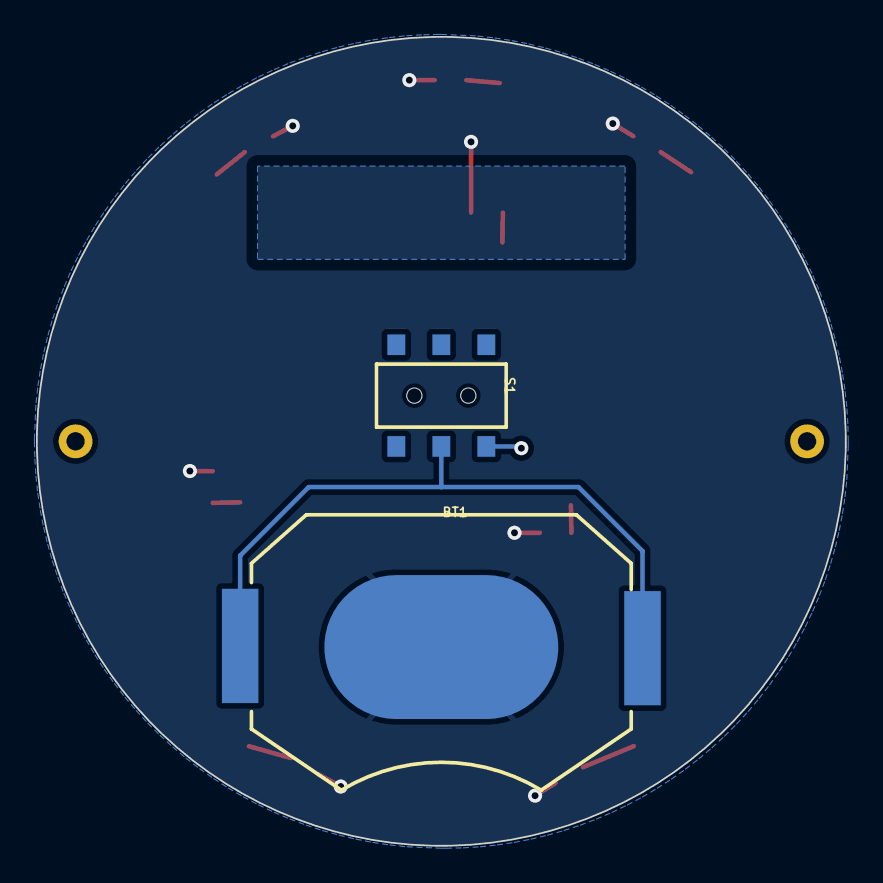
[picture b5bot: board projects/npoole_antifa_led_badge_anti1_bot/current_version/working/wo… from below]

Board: 2 copper layers, 44.9 x 44.9 mm, 20 parts (2 on the bottom side), 11 nets.

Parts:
BT1: BATTCON_20MM_4LEGS
D1, D2, D3, D4, D5, D6, D7, D8: LED-0603
E$3, E$4: 1X01_NO_SILK
R1, R2, R3, R4, R5, R6, R7, R8: 33; 0603
S1: SWITCH_DPDT_SMD_AYZ0202

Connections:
BTN: D4.A, R5.2
GND: R1.1, R2.1, R3.1, R4.1, R5.1, R6.1, R7.1, R8.1, S1.1
unnamed: D6.A, R1.2
unnamed: D1.A, R2.2
unnamed: D2.A, R3.2
unnamed: D3.A, R4.2
unnamed: D5.A, R6.2
unnamed: D7.A, R7.2
unnamed: D8.A, R8.2
unnamed: BT1.NEGATIVE, D1.C, D2.C, D3.C, D4.C, D5.C, D6.C, D7.C, D8.C
VCC: BT1.POSITIVE@1, BT1.POSITIVE@2, BT1.POSITIVE@3, BT1.POSITIVE@4, S1.2

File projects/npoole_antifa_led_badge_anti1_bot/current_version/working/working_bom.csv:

"Id";"Designator";"Footprint";"Quantity";"Designation";"Supplier and ref";
1;"D8,D7,D4,D3,D2,D1,D5,D6";"LED-0603";8;"";;;
2;"R5,R4,R6,R2,R8,R3,R7,R1";"0603";8;"33";;;
3;"E$3,E$4";"1X01_NO_SILK";2;"";;;
4;"S1";"SWITCH_DPDT_SMD_AYZ0202";1;"";;;
5;"BT1";"BATTCON_20MM_4LEGS";1;"";;;
